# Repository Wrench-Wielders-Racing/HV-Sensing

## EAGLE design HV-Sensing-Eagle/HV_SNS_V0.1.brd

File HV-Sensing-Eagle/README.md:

Add the EAGLE project files to this folder.

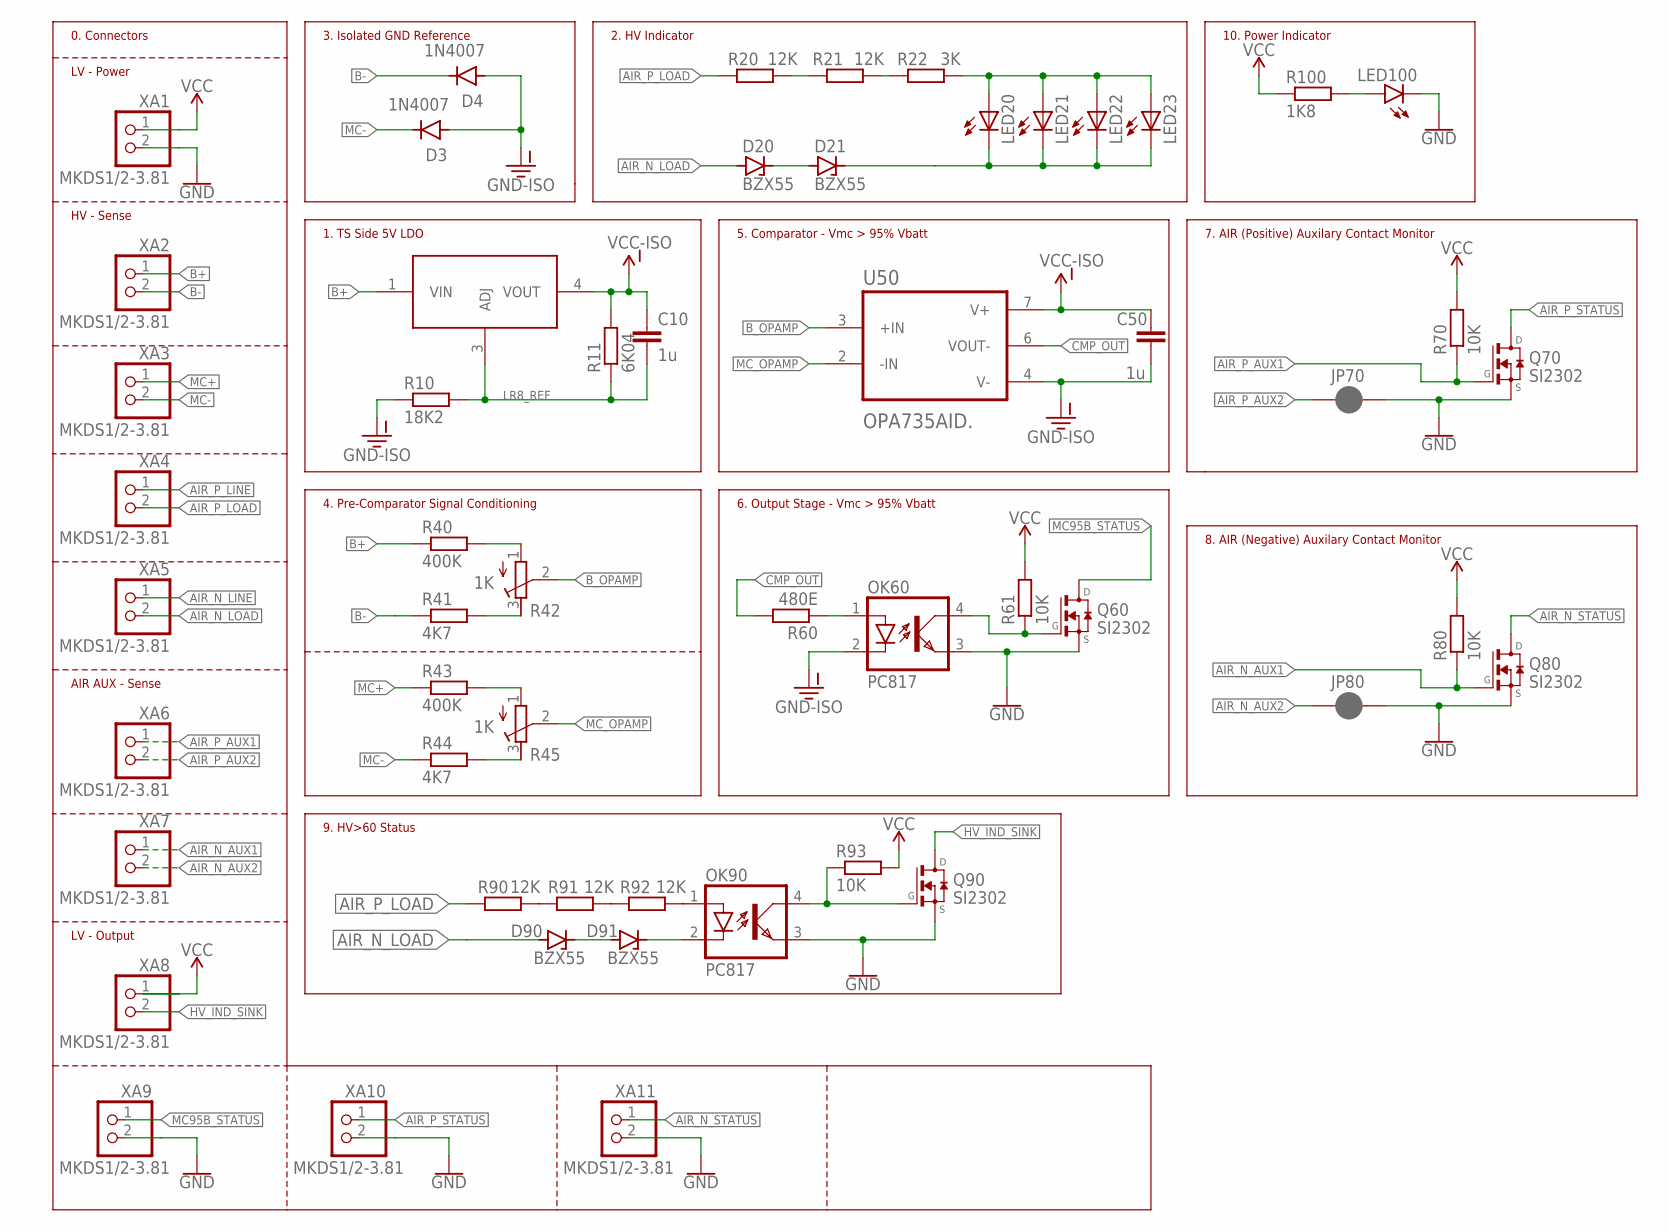
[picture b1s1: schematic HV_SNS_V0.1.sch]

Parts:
C10, C50: 1u; C0805
D3, D4: 1N4007; DO-41
D20, D21, D90, D91: BZX55; DO35Z10
JP70, JP80: JUMPER-SMT_2_NC_PASTE_SILK; SMT-JUMPER_2_NC_PASTE_SILK
LED20, LED21, LED22, LED23: LED5MM
LED100: LEDCHIP-LED0805; CHIP-LED0805
OK60, OK90: PC817; DIL04
Q60, Q70, Q80, Q90: SI2302; SOT23
R10: 18K2; R0805
R11: 6K04; R0805
R20, R21, R90, R91, R92: 12K; 0207/10
R22: 3K; 0207/10
R40, R43: 400K; 0207/10
R41, R44: 4K7; 0207/10
R42, R45: 1K; RTRIM3296W
R60: 480E; R0805
R61, R70, R80, R93: 10K; R0805
R100: 1K8; R0805
U10: LR8K4-G; PMX42_DPAK
U50: OPA735AID.; SO-8
XA1, XA2, XA3, XA4, XA5, XA6, XA7, XA8, XA9, XA10, XA11: MKDS1/2-3.81; PHOENIX_MKDS1/2-3.81

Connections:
AIR_N_AUX1: Q80.1 (G), R80.1, XA7.1
AIR_N_AUX2: JP80.1, XA7.2
AIR_N_LINE: XA5.1
AIR_N_LOAD: D20.A, D90.A, XA5.2
AIR_N_STATUS: Q80.3 (D), XA11.1
AIR_P_AUX1: Q70.1 (G), R70.1, XA6.1
AIR_P_AUX2: JP70.1, XA6.2
AIR_P_LINE: XA4.1
AIR_P_LOAD: R20.1, R90.1, XA4.2
AIR_P_STATUS: Q70.3 (D), XA10.1
B+: R40.1, U10.1 (VIN), XA2.1
B-: D4.C, R41.1, XA2.2
B_OPAMP: R42.2 (S), U50.3 (+IN)
CMP_OUT: R60.2, U50.6 (VOUT-)
GND: JP70.2, JP80.2, LED100.C, OK60.3 (EMIT), OK90.3 (EMIT), Q60.2 (S), Q70.2 (S), Q80.2 (S), Q90.2 (S), XA1.2, XA9.2, XA10.2, XA11.2
GND-ISO: C50.2, D3.A, D4.A, OK60.2 (C), R10.1, U50.4 (V-)
HV_IND_SINK: Q90.3 (D), XA8.2
LR8_REF: C10.2, R10.2, R11.1, U10.3 (ADJ)
MC95B_STATUS: Q60.3 (D), XA9.1
MC+: R43.1, XA3.1
MC-: D3.C, R44.1, XA3.2
MC_OPAMP: R45.2 (S), U50.2 (-IN)
unnamed: D20.C, D21.A
unnamed: LED20.A, LED21.A, LED22.A, LED23.A, R22.2
unnamed: D21.C, LED20.K (C), LED21.K (C), LED22.K (C), LED23.K (C)
unnamed: OK90.4 (COL), Q90.1 (G), R93.1
unnamed: R43.2, R45.1 (A)
unnamed: R44.2, R45.3 (E)
unnamed: R41.2, R42.3 (E)
unnamed: R40.2, R42.1 (A)
unnamed: OK60.1 (A), R60.1
unnamed: OK60.4 (COL), Q60.1 (G), R61.1
unnamed: R20.2, R21.1
unnamed: R21.2, R22.1
unnamed: OK90.1 (A), R92.2
unnamed: R91.2, R92.1
unnamed: R90.2, R91.1
unnamed: D91.C, OK90.2 (C)
unnamed: D90.C, D91.A
unnamed: LED100.A, R100.2
VCC: R61.2, R70.2, R80.2, R93.2, R100.1, XA1.1, XA8.1
VCC-ISO: C10.1, C50.1, R11.2, U10.4 (VOUT), U50.7 (V+)

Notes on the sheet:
0. Connectors
LV - Power
HV - Sense
AIR AUX - Sense
LV - Output
3. Isolated GND Reference
2. HV Indicator
1. TS Side 5V LDO
4. Pre-Comparator Signal Conditioning
5. Comparator - Vmc > 95% Vbatt
6. Output Stage - Vmc > 95% Vbatt
7. AIR (Positive) Auxilary Contact Monitor
8. AIR (Negative) Auxilary Contact Monitor
9. HV>60 Status
10. Power Indicator

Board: 2 copper layers, 54 parts (0 on the bottom side), 40 nets, no tracks yet.

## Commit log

2020-12-24 Changed file locations
2020-12-24 Added simulation folder
2020-12-25 Added PCB file

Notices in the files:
parts and their libraries:
SparkFun-Jumpers: Licensing: Creative Commons ShareAlike 4.0 International - https://creativecommons.org/licenses/by-sa/4.0
